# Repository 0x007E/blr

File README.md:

# `BLR` - Lead Battery Charger (Bleiakkuladeregler)

The `BLR` project is based on a pcb with a positive voltage regulator for battery charging (`PB137`). It can be used to charge [lead-batteries](#additional-information) with a voltage of 12V and observe the status of a battery during use.

| Experience | Level |
|:------------|:-----:|
| Soldering   |  |
| Mechanical  |  |

# Downloads

| Type      | File               | Description              |
|:---------:|:------------------:|:-------------------------|
| Simulation | [asc](https://github.com/0x007E/blr/raw/refs/heads/main/BLR.asc) | LTSpice Simulation | 
| Lochmaster | [lm4](https://github.com/0x007E/blr/raw/refs/heads/main/BLR.LM4) | Stripe grid circuit board | 
| Schematic | [pdf](https://github.com/0x007E/blr/releases/latest/download/schematic.pdf) / [cadlab](https://cadlab.io/project/28581/main/files) | Schematic files |
| Board | [pdf](https://github.com/0x007E/blr/releases/latest/download/pcb.pdf) / [cadlab](https://cadlab.io/project/28581/main/files) | Board file |
| Drill | [pdf](https://github.com/0x007E/blr/releases/latest/download/drill.pdf) | Drill file |
| PCB | [zip](https://github.com/0x007E/blr/releases/latest/download/kicad.zip) / [tar](https://github.com/0x007E/blr/releases/latest/download/kicad.tar.gz) | KiCAD/Gerber/BoM/Drill files |
| Mechanical | [zip](https://github.com/0x007E/blr/releases/latest/download/freecad.zip) / [tar](https://github.com/0x007E/blr/releases/latest/download/freecad.tar.gz) | FreeCAD/Housing and PCB (STEP) files     |

# Hardware

There are two parts of the hardware. The pcb and the housing of the `BLR`. The pcb is created with `KiCAD` and the housing with `FreeCAD`. All files are built with `github actions` so that they are ready for a production environment. The housing is printed with a 3D-printer (`Dremel 3D40`).

## PCB

The circuit board is populated on both sides (Top, Bottom). The best way for soldering is within a vapor phase soldering system.

### Top Layer

### Bottom Layer

## Mechanical

The housing has a tolerance of `0.2mm` on each side of the case. So the pcb should fit perfectly in the housing. The tolerance can be modified with `FreeCAD` in the `Parameter` Spreadsheet.

### Assembled

#### Exploded

# Setup

To setup the `BLR` the reference voltages of `TP1`, `TP2`, `TP3` and `TP4` needs to be adjusted.

| Point | Voltage | U<sub>In</sub> |
|:-----:|:-------:|:--------------:|
| `TP1` | ~2V5    | ~8V            | 
| `TP2` | ~2V5    | -              |
| `TP3` | ~2V5    | ~13V           |

> TP4 needs to be adjusted manually with an Ampermeter. If the current is > `100 mA` the charging LED (`J8`) should be on. This behaviour can be adjusted through `RV3`.

# Additional Information

| Type       | Link               | Description              |
|:----------:|:------------------:|:-------------------------|
| PB137 | [pdf](https://www.st.com/resource/en/datasheet/pb137.pdf) | Positive voltage regulator for battery charging datasheet |
| TL431 | [pdf](https://www.ti.com/lit/ds/symlink/tl431.pdf) | Precision voltage reference |
| LM358 | [pdf](https://www.ti.com/lit/ds/symlink/lm358.pdf) | Dual operational amplifier |
| Battery | [web](https://at.rs-online.com/web/p/bleiakkus/8431310) | Lead battery with 12V |

---

R. GAECHTER

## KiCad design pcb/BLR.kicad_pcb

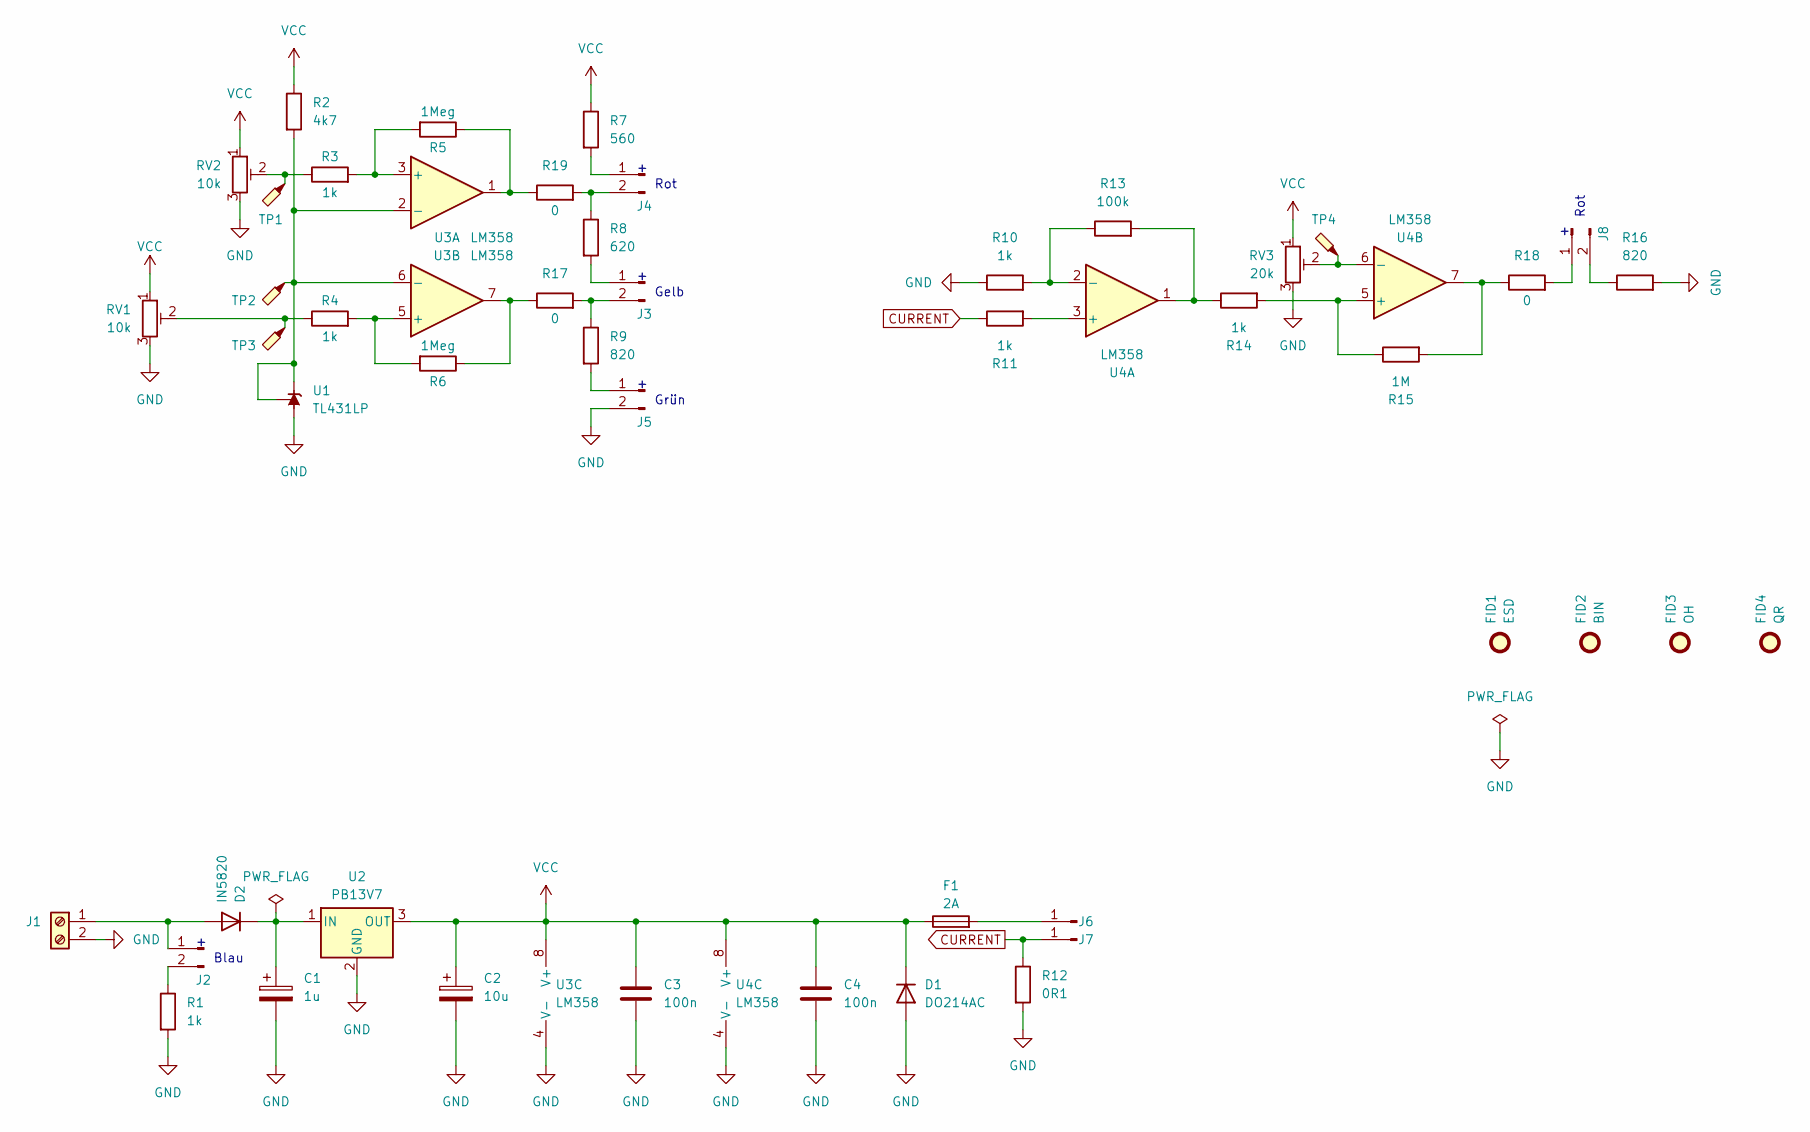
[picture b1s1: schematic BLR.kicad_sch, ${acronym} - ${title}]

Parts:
C1: 1u; CP_Radial_D6.3mm_P2.50mm
C2: 10u; CP_Radial_D6.3mm_P2.50mm
C3, C4: 100n; C_1206_3216Metric
D1: DO214AC; D_MELF
D2: IN5820; D_DO-201AD_P12.70mm_Horizontal
F1: 2A; Fuseholder_Clip-5x20mm_Littelfuse_111_Inline_P20.00x5.00mm_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
FID1: ESD; ESD-Logo_6.6x6mm_SilkScreen
FID2: BIN; WEEE-Logo_4.2x6mm_SilkScreen
FID3: OH; OSHW-Logo_5.7x6mm_SilkScreen
FID4: QR; QR_0x007e
J1: Screw_01x02; TerminalBlock_Phoenix_MKDS-1,5-2-5.08_1x02_P5.08mm_Horizont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
J2, J3, J4, J5, J8: Conn_01x02_Pin; WAGO_2060-402_998-404
J6, J7: Conn_01x01_Pin; CONN_QC_RCPT_0.250
R1, R3, R4, R10, R11, R14: 1k; R_1206_3216Metric
R2: 4k7; R_1206_3216Metric
R5, R6: 1Meg; R_1206_3216Metric
R7: 560; R_1206_3216Metric
R8: 620; R_1206_3216Metric
R9, R16: 820; R_1206_3216Metric
R12: 0R1; R_Axial_Power_L20.0mm_W6.4mm_P22.40mm
R13: 100k; R_1206_3216Metric
R15: 1M; R_1206_3216Metric
R17, R18, R19: 0; R_1206_3216Metric
RV1, RV2: 10k; Potentiometer_Bourns_3296W_Vertical
RV3: 20k; Potentiometer_Bourns_3314J_Vertical
TP1, TP2, TP3, TP4: TestPoint_Probe; TestPoint_Pad_D1.5mm
U1: TL431LP; TO-92_Wide
U2: PB13V7; TO-220-3_Vertical
U3, U4: LM358; SOP-8_3.9x4.9mm_P1.27mm

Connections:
CURRENT: J7.1, R11.1, R12.1
GND: C1.2, C2.2, C3.2, C4.2, D1.2 (A), J1.2, J5.2, R1.2, R10.1, R12.2, R16.2, RV1.3, RV2.3, RV3.3, U1.2 (A), U2.2 (GND), U3.4 (V-), U4.4 (V-)
unnamed: D2.2 (A), J1.1, J2.1
unnamed: C1.1, D2.1 (K), U2.1 (IN)
unnamed: J2.2, R1.1
unnamed: J3.1, R8.2
unnamed: J3.2, R9.1, R17.2
unnamed: J4.1, R7.2
unnamed: J4.2, R8.1, R19.2
unnamed: J5.1, R9.2
unnamed: F1.2, J6.1
unnamed: J8.1, R18.2
unnamed: J8.2, R16.1
unnamed: R3.1, RV2.2, TP1.1
unnamed: R4.1, RV1.2, TP3.1
unnamed: R13.2, R14.1, U4.1
unnamed: R15.2, R18.1, U4.7
unnamed: R6.1, R17.1, U3.7
unnamed: R5.1, R19.1, U3.1
unnamed: R2.2, TP2.1, U1.1 (REF), U1.3 (K), U3.2 (-), U3.6 (-)
unnamed: R3.2, R5.2, U3.3 (+)
unnamed: R4.2, R6.2, U3.5 (+)
unnamed: R11.2, U4.3 (+)
unnamed: R10.2, R13.1, U4.2 (-)
unnamed: R14.2, R15.1, U4.5 (+)
unnamed: RV3.2, TP4.1, U4.6 (-)
VCC: C2.1, C3.1, C4.1, D1.1 (K), F1.1, R2.1, R7.1, RV1.1, RV2.1, RV3.1, U2.3 (OUT), U3.8 (V+), U4.8 (V+)

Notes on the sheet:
Rot
Blau
Gelb
Grün

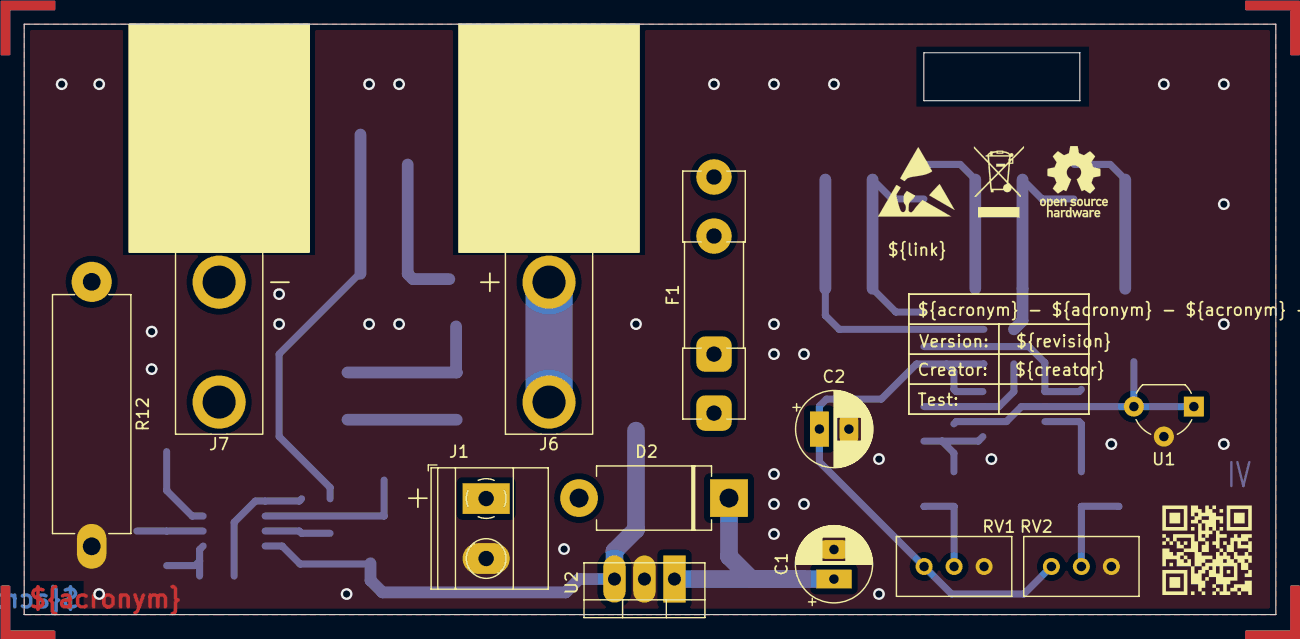
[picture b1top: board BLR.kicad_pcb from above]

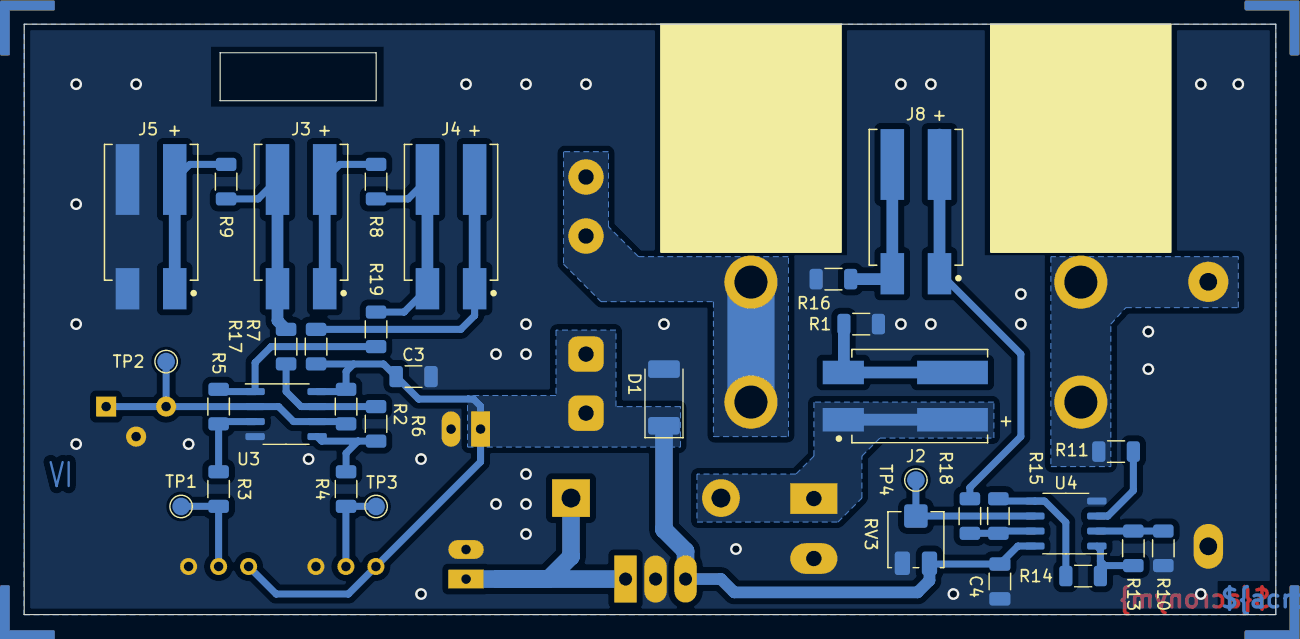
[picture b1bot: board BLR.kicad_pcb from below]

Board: 2 copper layers, 106.0 x 50.0 mm, 49 parts (33 on the bottom side), 27 nets.

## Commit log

2024-10-21 Add KiBot
2024-10-21 Add Actions
2024-10-21 Add README
2024-10-21 Add missing filter
2024-10-21 Update additional information
2024-10-21 Add font
2024-10-22 Fix heading
2024-10-22 Fix typos
2024-10-25 Change experience
2024-10-25 Cleanup README
2025-02-28 Extend filetypes
2025-02-28 Case refactoring
2025-02-28 Refresh images after refactoring
2025-02-28 Increment FreeCAD version
2025-02-28 Fix mirror settings
2025-02-28 Increase scaling
2025-02-28 Add value to BOM
2025-02-28 Rename download parts
2025-02-28 Remove wrong identifier
2025-02-28 Add extended dimensioning
2025-10-22 Increase FreeCAD version
2025-10-22 Change supply voltage value

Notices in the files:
README.md:
License CC By-NC-SA
parts and their libraries:
license: CC BY-NC-SA 4.0
